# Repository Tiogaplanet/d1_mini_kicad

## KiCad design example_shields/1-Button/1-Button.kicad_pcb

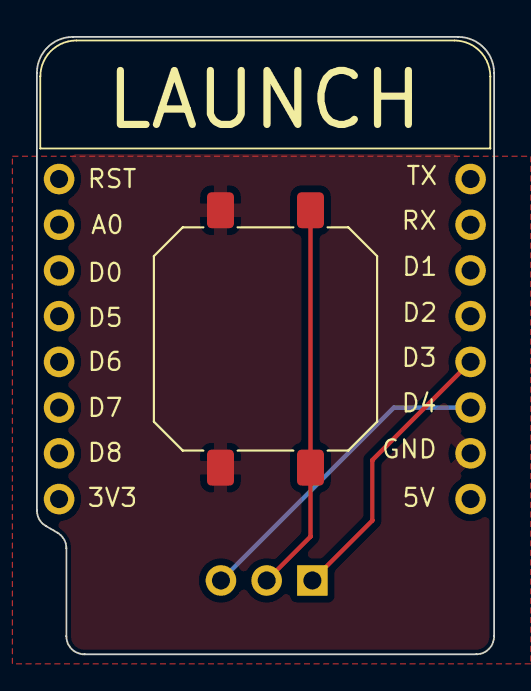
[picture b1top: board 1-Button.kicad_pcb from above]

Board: 2 copper layers, 25.4 x 34.3 mm, 3 parts (1 on the bottom side), 4 nets.

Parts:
J1: PinHeader_2x1x08_P2.54mm_D1_mini
J3: GPIO_SEL; PinHeader_1x03_P2.54mm_Horizontal
SW1: 1-Button; SW_Push_1P1T_NO_CK_PTS125Sx73SMTR

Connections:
/D3: J1.12 (D3), J3.1
/D4: J1.11 (D4), J3.3
GND: J1.10 (GND), SW1.1
unnamed: J3.2, SW1.2
